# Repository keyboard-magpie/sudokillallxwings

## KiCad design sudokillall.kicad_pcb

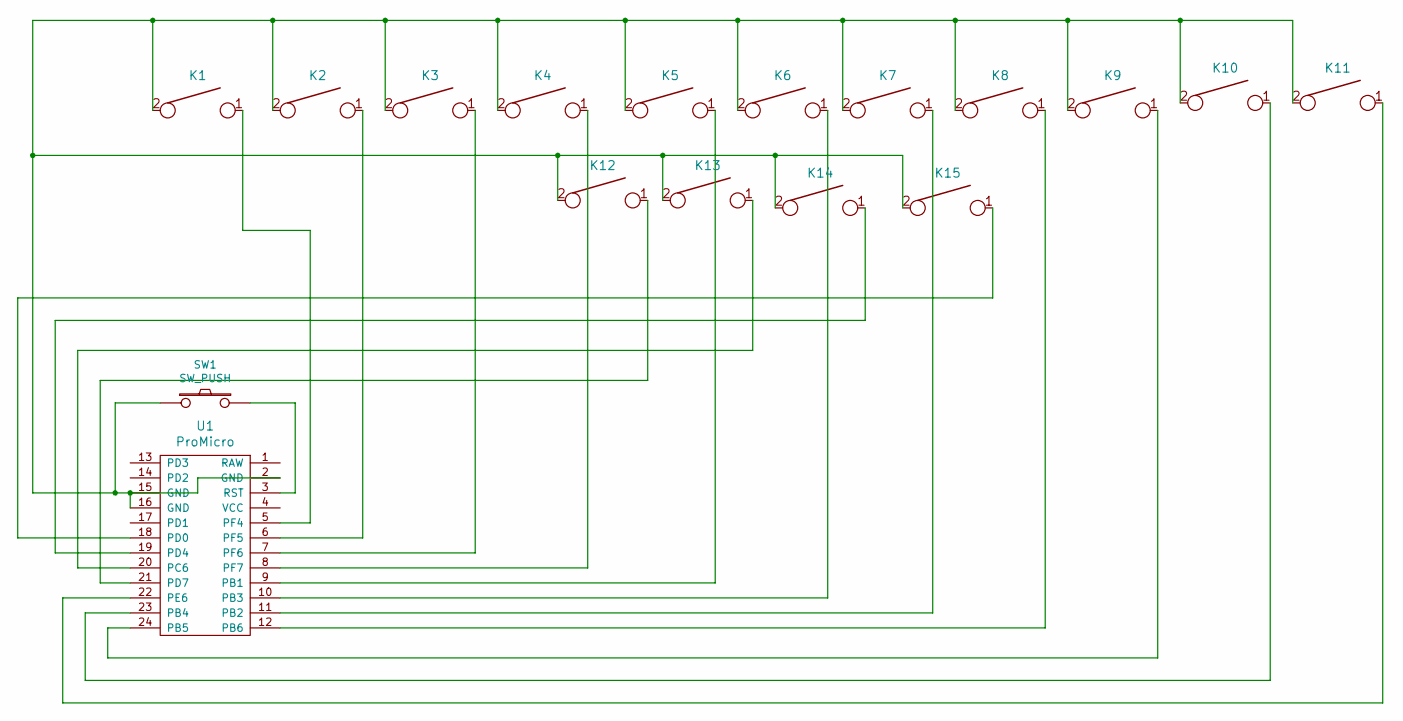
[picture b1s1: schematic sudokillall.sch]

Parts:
K1, K2, K3, K4, K5, K6, K7, K8, K9, K10, K11, K12, K13, K14, K15: KEYSW; SW_kailh_pg1350_1u
SW1: SW_PUSH; SW_TACT_ALPS_SKQGABE010
U1: ProMicro; Pro_Micro

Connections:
unnamed: K1.1, U1.5 (PF4)
unnamed: K1.2, K2.2, K3.2, K4.2, K5.2, K6.2, K7.2, K8.2, K9.2, K10.2, K11.2, K12.2, K13.2, K14.2, K15.2, SW1.1, U1.2 (GND), U1.15 (GND), U1.16 (GND)
unnamed: K2.1, U1.6 (PF5)
unnamed: K3.1, U1.7 (PF6)
unnamed: K4.1, U1.8 (PF7)
unnamed: K5.1, U1.9 (PB1)
unnamed: K6.1, U1.10 (PB3)
unnamed: K7.1, U1.11 (PB2)
unnamed: K8.1, U1.12 (PB6)
unnamed: K9.1, U1.24 (PB5)
unnamed: K10.1, U1.23 (PB4)
unnamed: K11.1, U1.22 (PE6)
unnamed: K12.1, U1.21 (PD7)
unnamed: K13.1, U1.20 (PC6)
unnamed: K14.1, U1.19 (PD4)
unnamed: K15.1, U1.18 (PD0)
unnamed: SW1.2, U1.3 (RST)

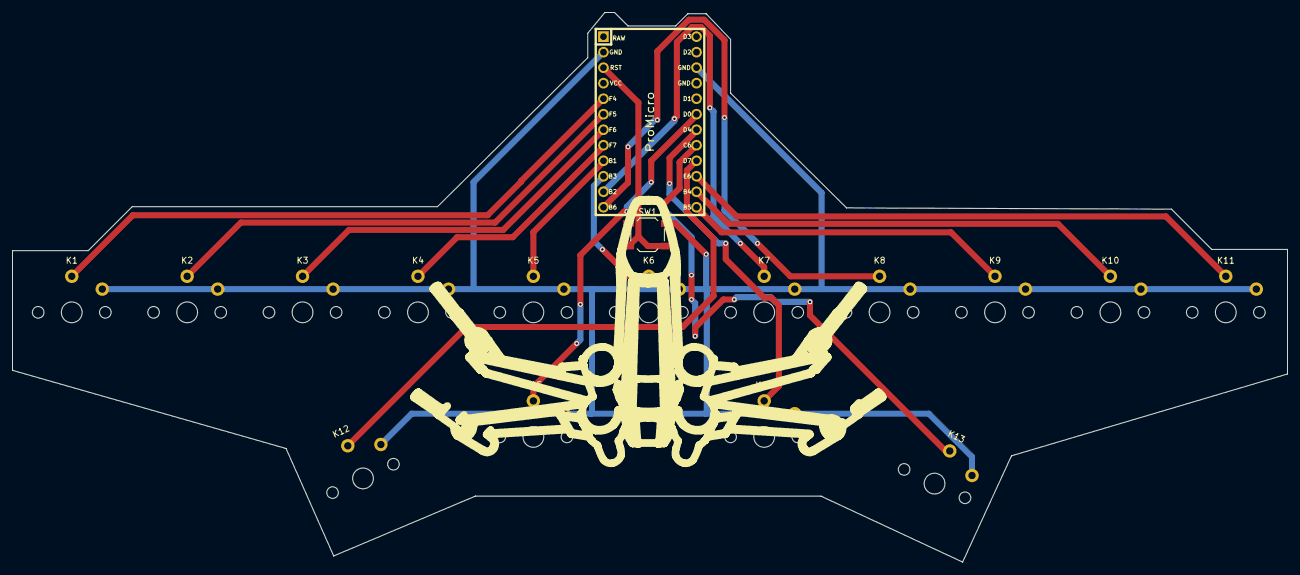
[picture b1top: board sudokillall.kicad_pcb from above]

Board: 2 copper layers, 208.8 x 90.0 mm, 17 parts (0 on the bottom side), 17 nets.

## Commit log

2020-12-22 Create dot
